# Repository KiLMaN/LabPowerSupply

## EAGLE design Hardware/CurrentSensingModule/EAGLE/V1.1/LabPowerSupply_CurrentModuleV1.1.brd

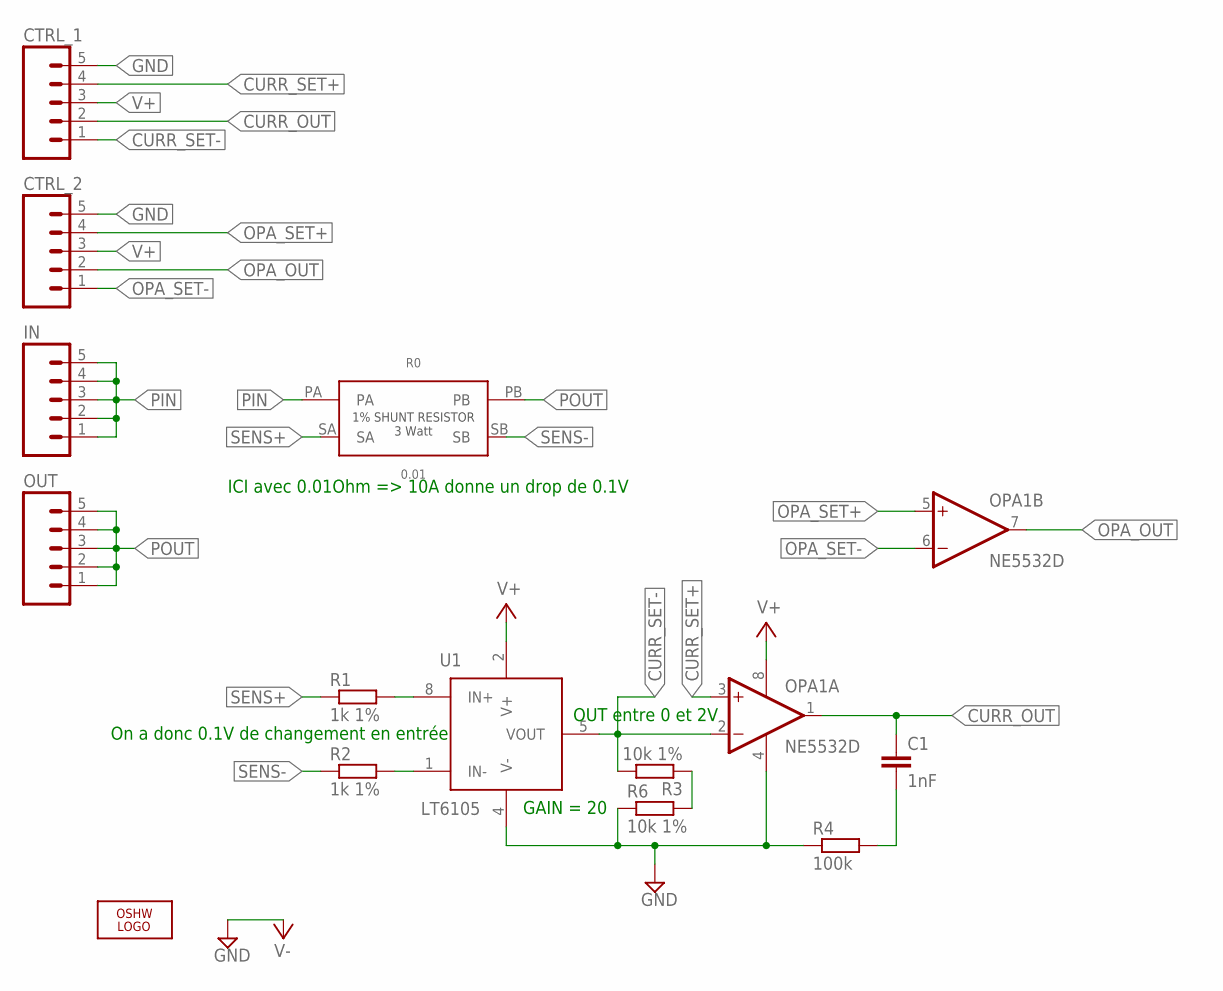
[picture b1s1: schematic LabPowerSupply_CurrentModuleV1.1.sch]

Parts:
C1: 1nF; C1206K
CTRL_1, CTRL_2: M05PTH_LONGPADS; 1X05_LONGPADS
IN: M05PTH_LONGPADS; 1X05_LONGPADS
LOGO1: OSHW_LOGO_FILLX0150-NT; OSHW_FILLX150_NOTEXT
OPA1: NE5532D; SO08
OUT: M05PTH_LONGPADS; 1X05_LONGPADS
R0: 0.01; 3637R
R1, R2: 1k 1%; R1206
R3, R6: 10k 1%; R1206
R4: 100k; R1206
U1: LT6105; MSOP_8

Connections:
CURR_OUT: C1.1, CTRL_1.2, OPA1.1 (OUT)
CURR_SET+: CTRL_1.4, OPA1.3 (+IN)
CURR_SET-: CTRL_1.1, OPA1.2 (-IN), R3.2, U1.5 (VOUT)
GND: CTRL_1.5, CTRL_2.5, OPA1.4 (V-), R4.1, R6.1, U1.4 (V-)
unnamed: R1.2, U1.8 (IN+)
unnamed: R2.2, U1.1 (IN-)
unnamed: C1.2, R4.2
unnamed: R3.1, R6.2
OPA_OUT: CTRL_2.2, OPA1.7 (OUT)
OPA_SET+: CTRL_2.4, OPA1.5 (+IN)
OPA_SET-: CTRL_2.1, OPA1.6 (-IN)
PIN: IN.1, IN.2, IN.3, IN.4, IN.5, R0.PA
POUT: OUT.1, OUT.2, OUT.3, OUT.4, OUT.5, R0.PB
SENS+: R0.SA, R1.1
SENS-: R0.SB, R2.1
V+: CTRL_1.3, CTRL_2.3, OPA1.8 (V+), U1.2 (V+)

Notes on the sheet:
OUT entre 0 et 2V
GAIN = 20
ICI avec 0.01Ohm => 10A donne un drop de 0.1V
On a donc 0.1V de changement en entrée

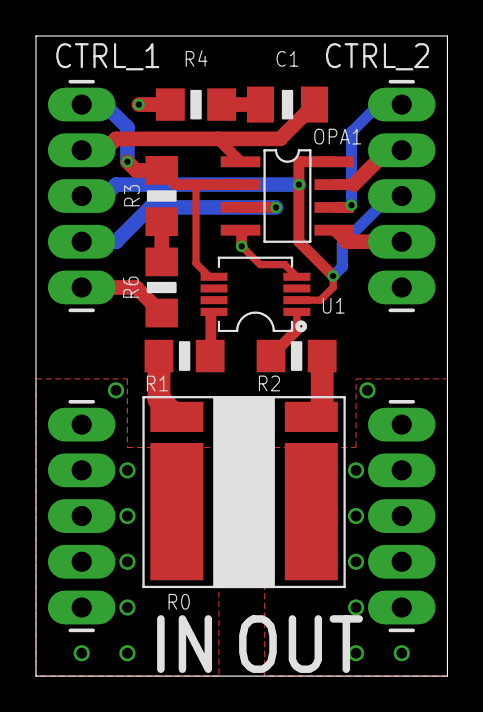
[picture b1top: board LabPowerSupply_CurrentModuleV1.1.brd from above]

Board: 2 copper layers, 22.9 x 35.6 mm, 14 parts (1 on the bottom side), 16 nets.

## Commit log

2014-05-24 Add Current Sensing Module
    Current sensing from 0 to 10 Amps outputs 0 to 2 V
2014-07-02 Update Current Module
    Error in footprint of the LT6105 corrected

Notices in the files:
parts and their libraries:
SparkFun-Connectors: Licensing: CC v3.0 Share-Alike You are welcome to use this library for commercial purposes.
